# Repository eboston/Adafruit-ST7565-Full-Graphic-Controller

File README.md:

# Adafruit-ST7565-Full-Graphic-Controller
3D Printer Controller based around the Adafruit ST7565 display

This is a simple project I started to utilize a couple displays I had gotten from 
Adafruit (http://www.adafruit.com/products/250).  Initially this is just for the
RAMPS 1.4 board utilizing the basic smart adapter running Marlin.  Plans are to expand 
the supported platforms to include the Smoothieboard with GLCD shield and the Printrboard 
Rev F4.

Initial support has been added to the devlopment branch of Marlin.

The PCB is Rev B and has not been built or tested yet.  It contains fixes for problems found in the Rev A board.

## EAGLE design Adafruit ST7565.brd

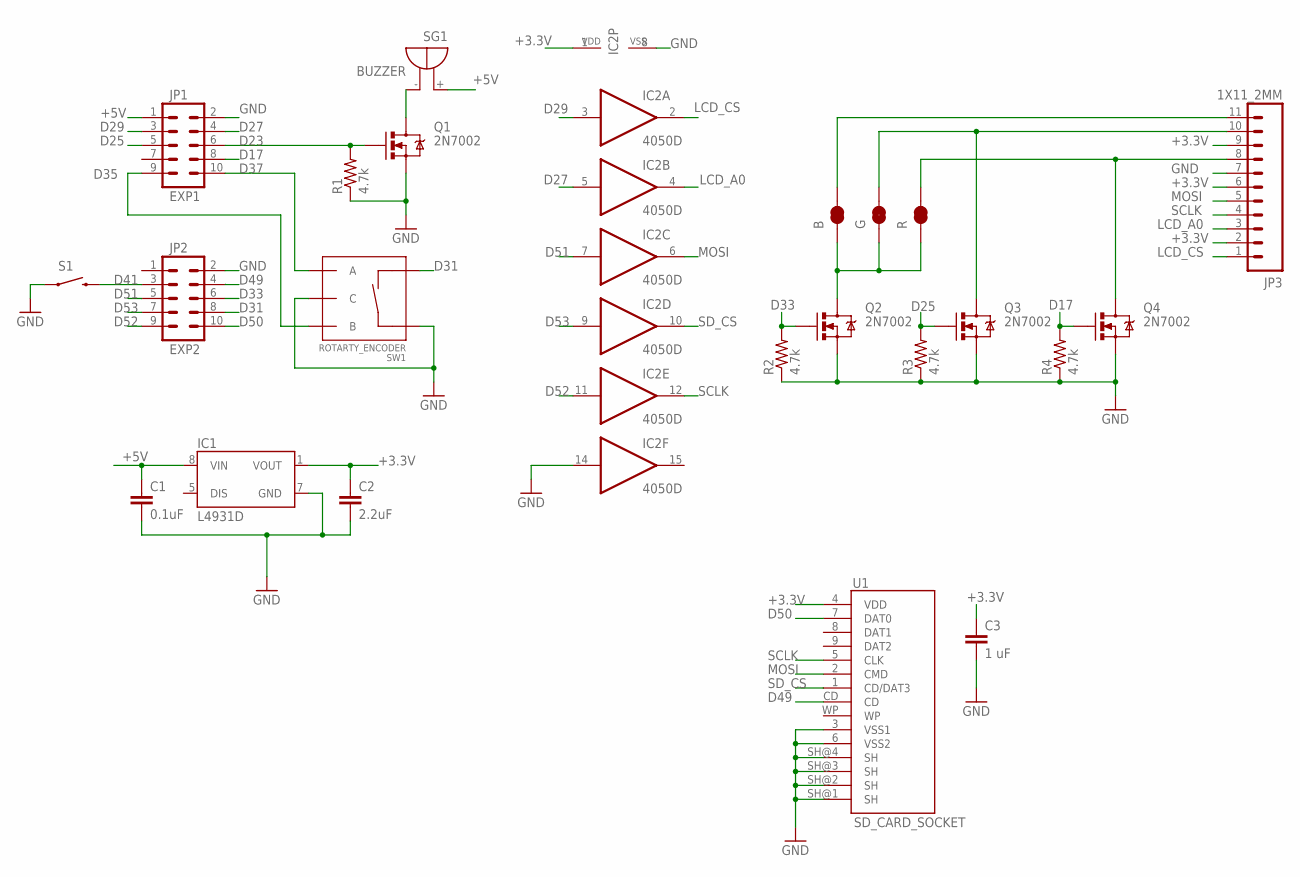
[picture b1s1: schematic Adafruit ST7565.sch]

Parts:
B: Blue; PAD-JUMPER-2-NC_BY_TRACE_YES_SILK
C1: 0.1uF; 1206
C2: 2.2uF; 1206
C3: 1 uF; 1206
G: Green; PAD-JUMPER-2-NC_BY_TRACE_YES_SILK
IC1: L4931D; SO08
IC2: 4050D; SO16
JP1: EXP1; 2X5-SHROUDED
JP2: EXP2; 2X5-SHROUDED
JP3: 1X11_2MM
Q1, Q2, Q3, Q4: 2N7002; SOT23-3
R: Red; PAD-JUMPER-2-NC_BY_TRACE_YES_SILK
R1, R2, R3, R4: 4.7k; 1206
S1: SWITCH-MOMENTARY-2PTH; TACTILE-PTH
SG1: BUZZER; F/QMBIII
SW1: ROTARTY_ENCODER; ROTARY_ENC_PLAIN
U1: SD_CARD_SOCKET; SD_1:1

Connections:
+3.3V: C2.1, C3.1, IC1.1 (VOUT), IC2.1 (VDD), JP3.2, JP3.6, JP3.9, U1.4 (VDD)
+5V: C1.1, IC1.8 (VIN), JP1.1, SG1.+
D17: JP1.8, Q4.1 (G), R4.2
D23: JP1.6, Q1.1 (G), R1.2
D25: JP1.5, Q3.1 (G), R3.2
D27: IC2.5 (I), JP1.4
D29: IC2.3 (I), JP1.3
D31: JP2.8, SW1.SW-
D33: JP2.6, Q2.1 (G), R2.2
D35: JP1.9, SW1.B
D37: JP1.10, SW1.A
D41: JP2.3, S1.3 (2)
D49: JP2.4, U1.CD
D50: JP2.10, U1.7 (DAT0)
D51: IC2.7 (I), JP2.5
D52: IC2.11 (I), JP2.9
D53: IC2.9 (I), JP2.7
GND: C1.2, C2.2, C3.2, IC1.7 (GND), IC2.8 (VSS), IC2.14 (I), JP1.2, JP2.2, JP3.7, Q1.2 (S), Q2.2 (S), Q3.2 (S), Q4.2 (S), R1.1, R2.1, R3.1, R4.1, S1.1, SW1.C, SW1.SW+, U1.3 (VSS1), U1.6 (VSS2), U1.SH@1 (SH), U1.SH@2 (SH), U1.SH@3 (SH), U1.SH@4 (SH)
LCD_A0: IC2.4 (O), JP3.3
LCD_CS: IC2.2 (O), JP3.1
MOSI: IC2.6 (O), JP3.5, U1.2 (CMD)
unnamed: Q1.3 (D), SG1.-
unnamed: B.1, G.1, Q2.3 (D), R.1
unnamed: B.2, JP3.11
unnamed: G.2, JP3.10, Q3.3 (D)
unnamed: JP3.8, Q4.3 (D), R.2
SCLK: IC2.12 (O), JP3.4, U1.5 (CLK)
SD_CS: IC2.10 (O), U1.1 (CD/DAT3)

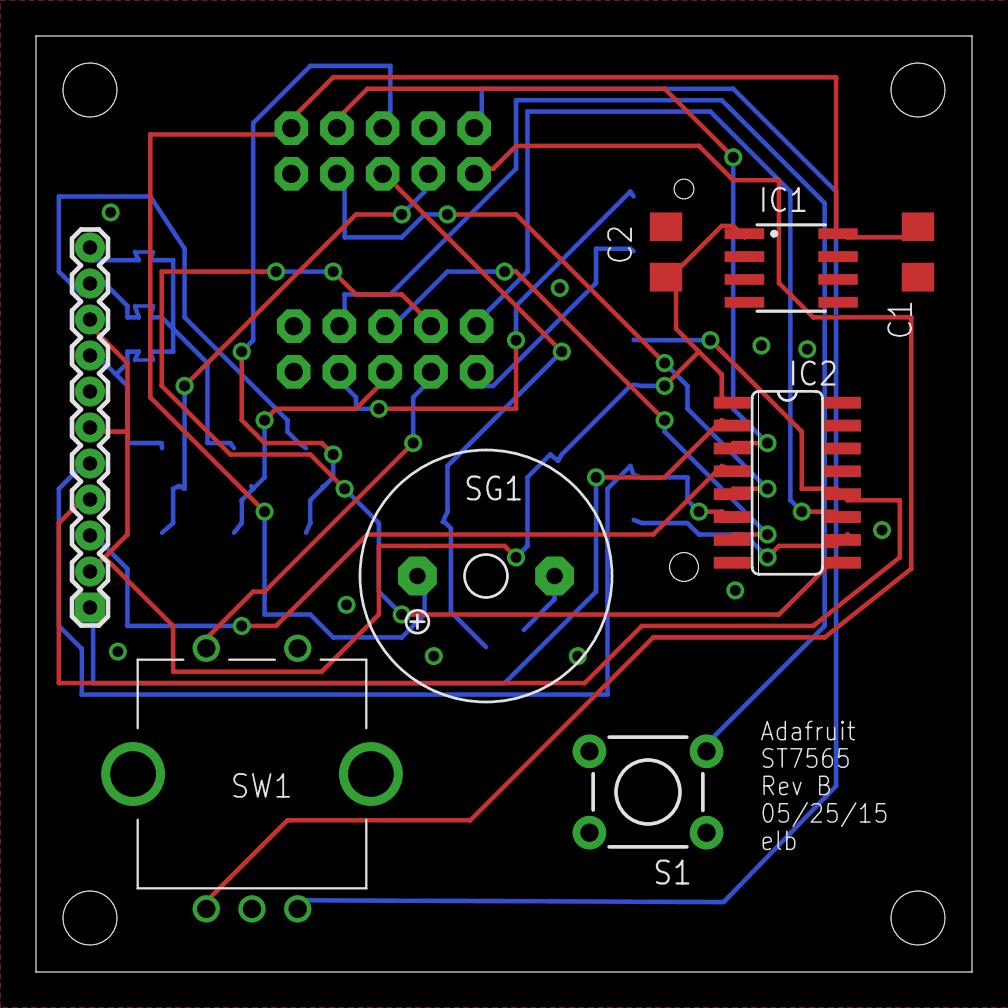
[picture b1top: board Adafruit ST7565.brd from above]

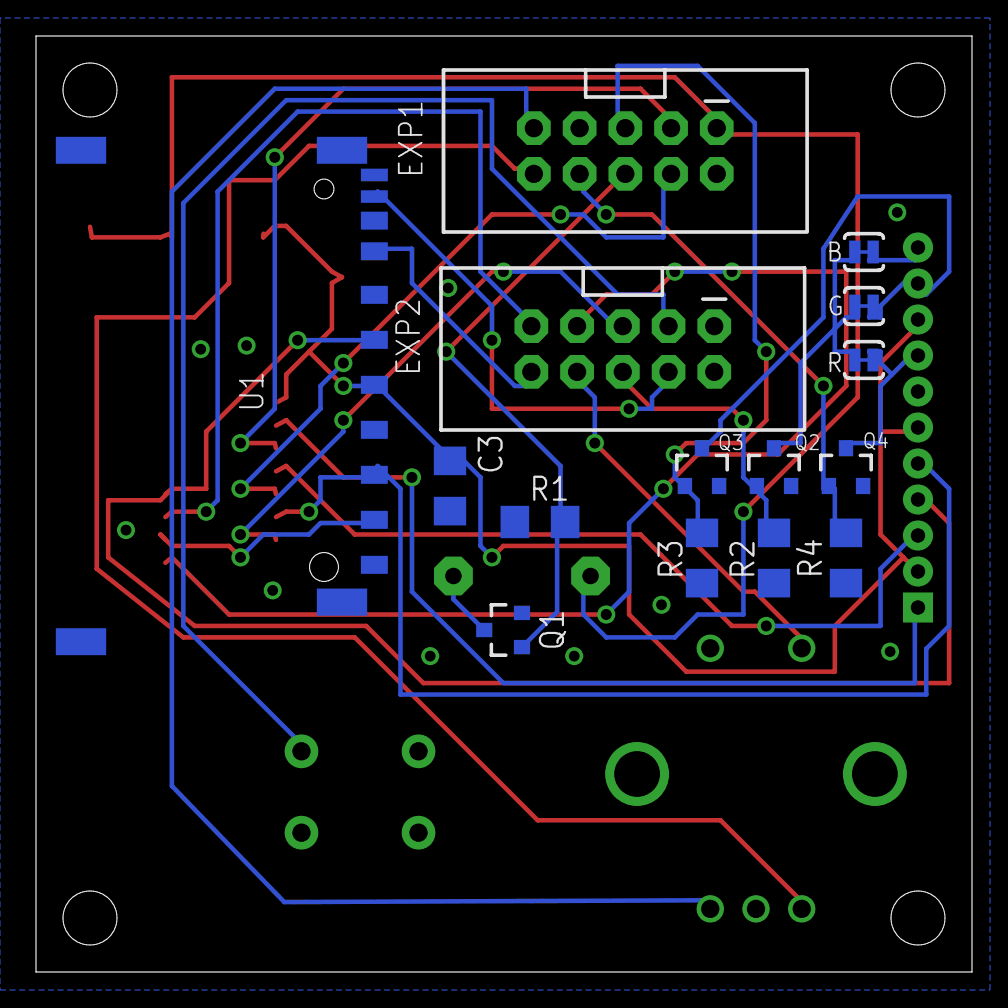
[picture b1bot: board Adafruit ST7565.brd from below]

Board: 2 copper layers, 52.0 x 52.0 mm, 23 parts (15 on the bottom side), 28 nets.

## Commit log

2015-05-18 :circus_tent: Added .gitattributes & .gitignore files
2015-05-18 Initial Files
    Now it begins
2015-05-18 .gitignore
    Ignore Eagle CAD backup and temporary files
2015-05-25 Rev B
2015-06-03 Not needed

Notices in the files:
parts and their libraries:
SparkFun-Connectors: Licensing: Creative Commons ShareAlike 4.0 International - https://creativecommons.org/licenses/by-sa/4.0
